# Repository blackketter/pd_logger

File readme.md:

# USB-C Power Delivery Measurement Tools

This repository contains two DIY gadgets to monitor and log **USB-C Power Delivery (PD)**.  
Both devices are designed to be easy to build, hackable, and useful for makers who want to explore USB-C PD.

---

## ✨ Features

- **DIY Power Meter**  
  Small device with an OLED display showing **voltage, current, and power** in real time.  
  Powered by an STM32 microcontroller.

- **PD Logger**  
  Wi-Fi enabled device based on ESP-01s.  
  Logs **voltage, current, and power** for several hours and serves interactive plots in any web browser.

---

## 📷 Devices

### Power Meter

### PD Logger

---

## 🛠️ How it works

- **USB-C connectors**: male on the input side, female on the output side.  
- **CC & VCONN lines** are passed through to handle PD voltage negotiation.  
- **Shunt resistor (50 mΩ)** allows precise current measurement.  
- **INA219 sensor** measures voltage and current via I²C.  
- **Step-down converter** generates 3.3 V from 5–20 V input.  
- **MCUs**: STM32 with OLED display (Power Meter), ESP-01s with Wi-Fi (PD Logger).  

---

## 📦 Hardware

- **Schematics & PCB files** → in this repo (`/electronics`)  
- **PCBs manufactured by** [JLCPCB](https://jlcpcb.com)  
- **3D printable cases** → in `/mechanics`  
- **Firmware** → in `/software`

All production data is included in `/electronics` so you can **order, print, and build your own devices**.

---

## 🌐 Usage

- **Power Meter**: plug between charger and device → read values on the display.  
- **PD Logger**: connect to your local Wi-Fi, then open `http://pd-logger.local` → see live values.  
  - Update interval: 5 seconds  
  - Logging capacity: several hours  
  - Data download as CSV file  
  - Interactive plots for Voltage / Current / Power over time  

---

## 📄 License

This project is licensed under the  
**Creative Commons Attribution-NonCommercial-ShareAlike 4.0 International (CC BY-NC-SA 4.0)** license.  

You are free to **share and adapt** the material, **for non-commercial purposes only**,  
as long as you provide proper attribution and distribute your contributions under the same license.  

For details, see the [LICENSE](LICENSE) file.  

---

## 🙌 Acknowledgments

- [Hackaday CH224K USB PD Decoy project](https://hackaday.io/) for inspiration

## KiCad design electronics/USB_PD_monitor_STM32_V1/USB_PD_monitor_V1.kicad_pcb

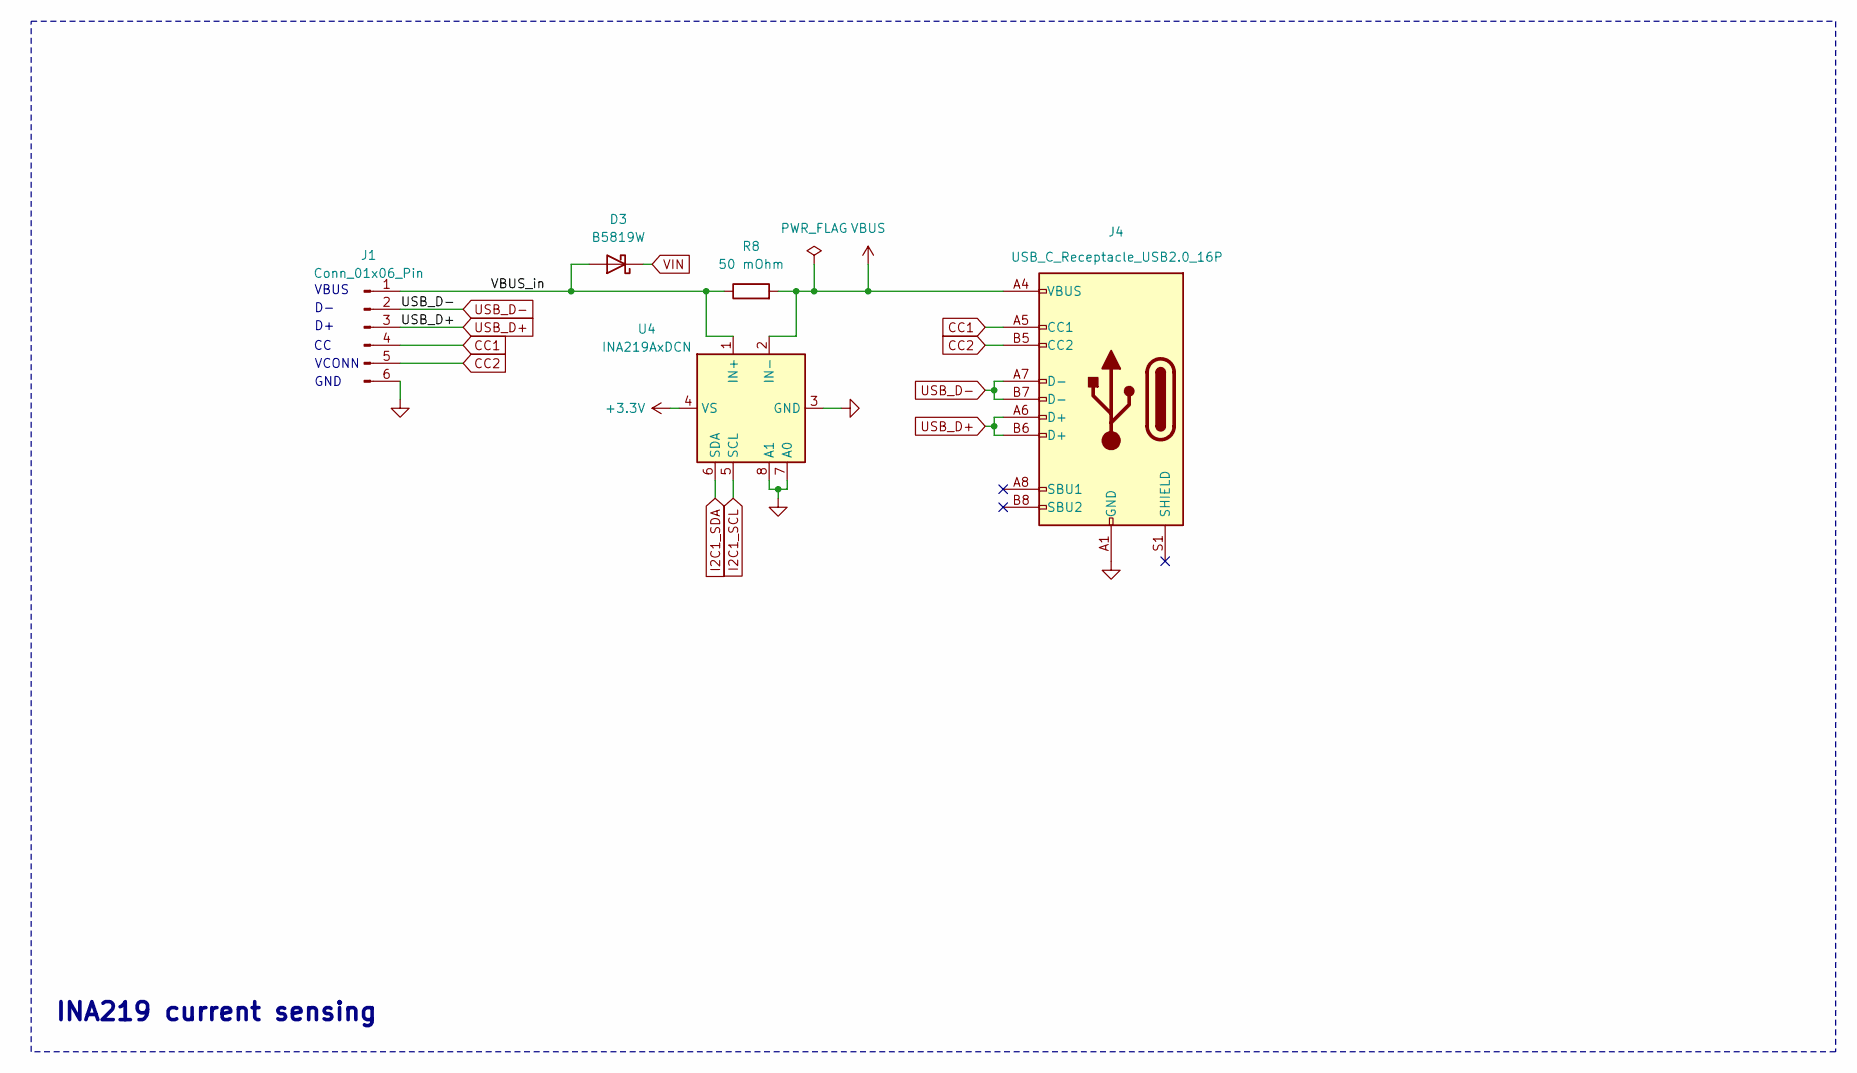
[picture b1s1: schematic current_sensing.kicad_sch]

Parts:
D3: B5819W; D_SOD-123; LCSC C8598
J1: Conn_01x06_Pin; header_90degree_01x06_back
J4: USB_C_Receptacle_USB2.0_16P; USB_C_Receptacle; LCSC C709357
R8: 50 mOhm; R_2512_6332Metric; LCSC C154681
U4: INA219AxDCN; SOT-23-8; LCSC C87469

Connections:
+3.3V: U4.4 (VS); also elsewhere on the board
/current_sensing/VBUS_in: D3.2 (A), J1.1, R8.1, U4.1 (IN+)
CC1: J1.4, J4.A5 (CC1)
CC2: J1.5, J4.B5 (CC2)
GND: J1.6, J4.A1 (GND), J4.A12 (GND), J4.B1 (GND), J4.B12 (GND), U4.3 (GND), U4.7 (A0), U4.8 (A1); also elsewhere on the board
I2C1_SCL: U4.5 (SCL); also elsewhere on the board
I2C1_SDA: U4.6 (SDA); also elsewhere on the board
USB_D+: J1.3, J4.A6 (D+), J4.B6 (D+)
USB_D-: J1.2, J4.A7 (D-), J4.B7 (D-)
VBUS: J4.A4 (VBUS), J4.A9 (VBUS), J4.B4 (VBUS), J4.B9 (VBUS), R8.2, U4.2 (IN-)
VIN: D3.1 (K); also elsewhere on the board

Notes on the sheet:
VBUS
VCONN
GND
INA219 current sensing

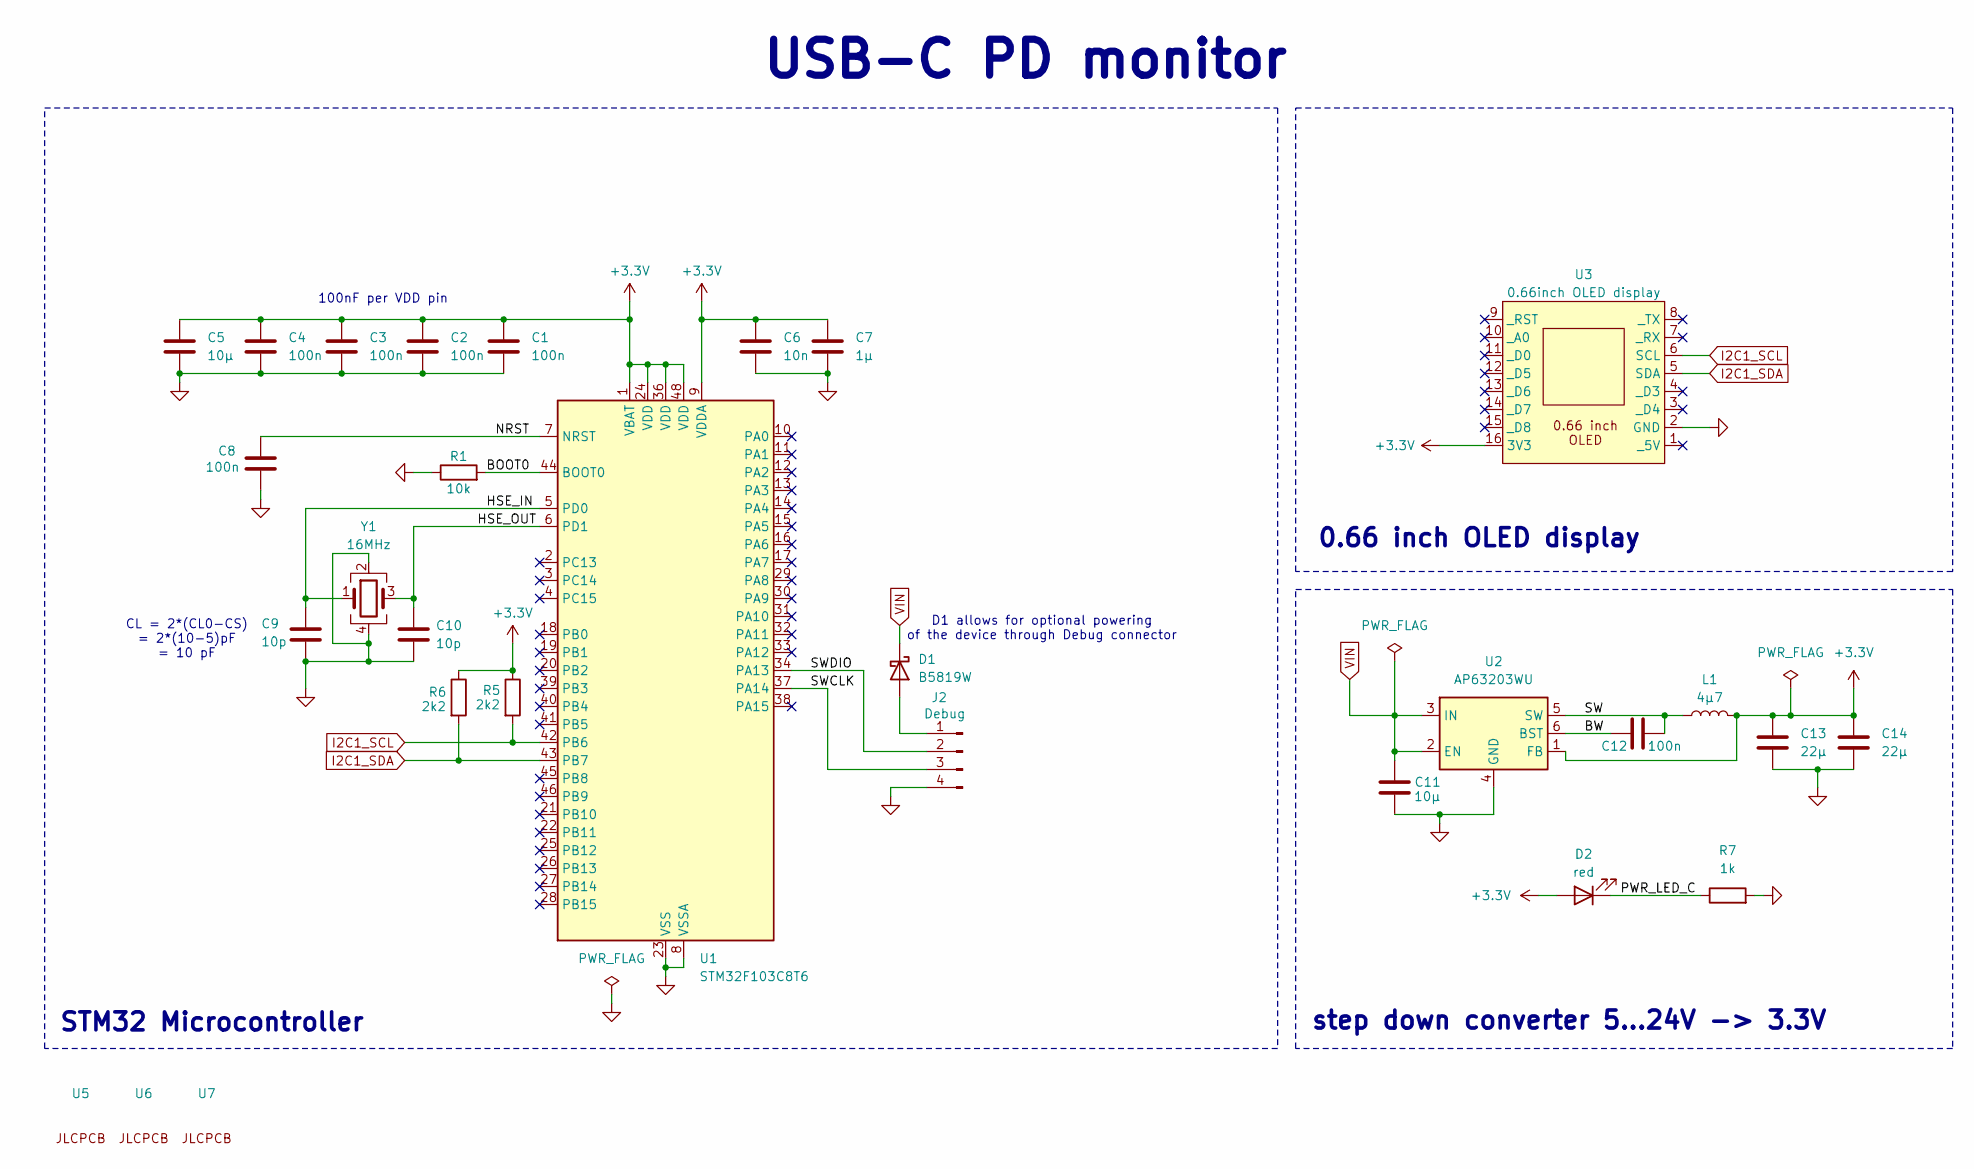
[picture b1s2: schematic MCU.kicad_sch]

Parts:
C1, C2, C3, C4, C8: 100n; C_0402_1005Metric; LCSC C1525
C5: 10µ; C_0603_1608Metric; LCSC C19702
C6: 10n; C_0402_1005Metric; LCSC C15195
C7: 1µ; C_0603_1608Metric; LCSC C15849
C9, C10: 10p; C_0402_1005Metric; LCSC C32949
C11: 10µ; C_0805_2012Metric; LCSC C440198
C12: 100n; C_0603_1608Metric; LCSC C14663
C13, C14: 22µ; C_0805_2012Metric; LCSC C45783
D1: B5819W; D_SOD-123; LCSC C8598
D2: red; LED_0603_1608Metric; LCSC C2286
J2: Debug; 4pin
L1: 4µ7; L_APV_APH0420; LCSC C133193
R1: 10k; R_0603_1608Metric; LCSC C25804
R5, R6: 2k2; R_0402_1005Metric; LCSC C25879
R7: 1k; R_0402_1005Metric; LCSC C11702
U1: STM32F103C8T6; LQFP-48_7x7mm_P0.5mm; LCSC C8734
U2: AP63203WU; TSOT-23-6; LCSC C780769
U3: 0.66inch OLED display; OLED_display_0_66
U5, U6, U7: JLC_tooling_hole
Y1: 16MHz; Crystal_SMD_3225-4Pin_3.2x2.5mm; LCSC C112972

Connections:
+3.3V: C1.1, C2.1, C3.1, C4.1, C5.1, C6.1, C7.1, C13.1, C14.1, D2.2 (A), L1.2, R5.1, R6.1, U1.1 (VBAT), U1.9 (VDDA), U1.24 (VDD), U1.36 (VDD), U1.48 (VDD), U2.1 (FB), U3.16 (3V3); also elsewhere on the board
/MCU/BOOT0: R1.2, U1.44 (BOOT0)
/MCU/BW: C12.1, U2.6 (BST)
/MCU/HSE_IN: C9.1, U1.5 (PD0), Y1.1
/MCU/HSE_OUT: C10.1, U1.6 (PD1), Y1.3
/MCU/NRST: C8.1, U1.7 (NRST)
/MCU/PWR_LED_C: D2.1 (K), R7.1
/MCU/SW: C12.2, L1.1, U2.5 (SW)
/MCU/SWCLK: J2.3, U1.37 (PA14)
/MCU/SWDIO: J2.2, U1.34 (PA13)
GND: C1.2, C2.2, C3.2, C4.2, C5.2, C6.2, C7.2, C8.2, C9.2, C10.2, C11.2, C13.2, C14.2, J2.4, R1.1, R7.2, U1.8 (VSSA), U1.23 (VSS), U1.35 (VSS), U1.47 (VSS), U2.4 (GND), U3.2 (GND), Y1.2, Y1.4; also elsewhere on the board
I2C1_SCL: R5.2, U1.42 (PB6), U3.6 (SCL); also elsewhere on the board
I2C1_SDA: R6.2, U1.43 (PB7), U3.5 (SDA); also elsewhere on the board
unnamed: D1.2 (A), J2.1
VIN: C11.1, D1.1 (K), U2.2 (EN), U2.3 (IN); also elsewhere on the board

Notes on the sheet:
100nF per VDD pin
step down converter 5...24V -> 3.3V
CL = 2*(CL0-CS) = 2*(10-5)pF = 10 pF
D1 allows for optional powering of the device through Debug connector
0.66 inch OLED display
STM32 Microcontroller
USB-C PD monitor

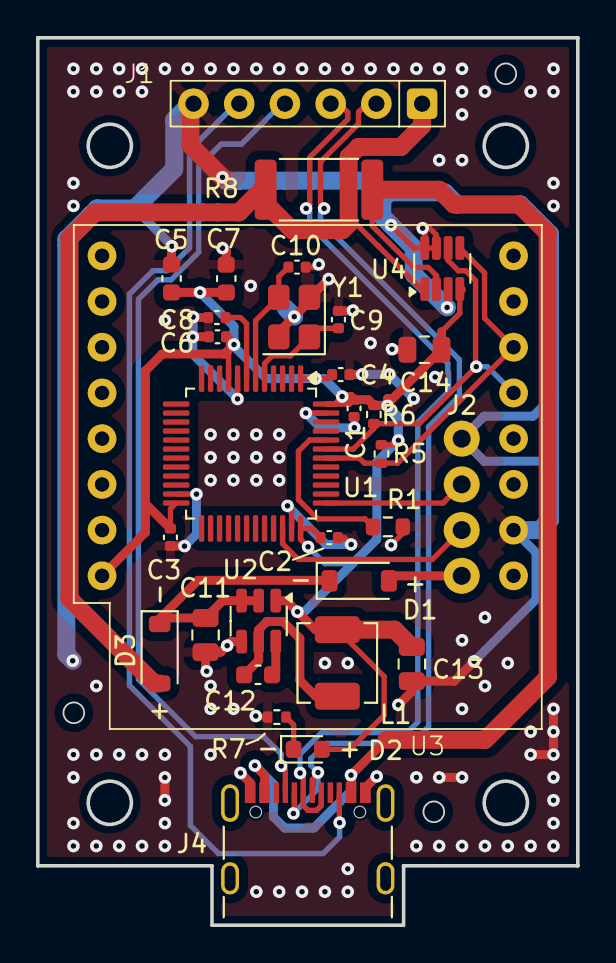
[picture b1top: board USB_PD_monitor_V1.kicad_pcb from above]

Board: 2 copper layers, 30.0 x 49.3 mm, 34 parts (0 on the bottom side), 21 nets.

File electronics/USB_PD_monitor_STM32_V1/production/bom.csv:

Designator,Footprint,Quantity,Value,LCSC Part #
"C1, C2, C3, C4, C8",0402,5,100n,C1525
"C10, C9",0402,2,10p,C32949 
C11,0805,1,10µ,C440198
C12,0603,1,100n,C14663
"C13, C14",0805,2,22µ,C45783
C5,0603,1,10µ,C19702 
C6,0402,1,10n,C15195
C7,0603,1,1µ,C15849
"D1, D3",D_SOD-123,2,B5819W,C8598
D2,0603,1,red,C2286
J1,header_90degree_01x06_back,1,Conn_01x06_Pin,
J2,4pin,1,Debug,
J4,USB_C_Receptacle,1,USB_C_Receptacle_USB2.0_16P,C709357
L1,L_APV_APH0420,1,4µ7,C133193
R1,0603,1,10k,C25804 
"R5, R6",0402,2,2k2,C25879
R7,0402,1,1k,C11702
R8,2512,1,50 mOhm,C154681
U1,LQFP-48_7x7mm_P0.5mm,1,STM32F103C8T6,C8734
U2,TSOT-23-6,1,AP63203WU,C780769
U3,OLED_display_0_66,1,0.66inch OLED display,
U4,SOT-23-8,1,INA219AxDCN,C87469
"U5, U6, U7",JLC_tooling_hole,3,~,
Y1,Crystal_SMD_3225-4Pin_3.2x2.5mm,1,16MHz,C112972

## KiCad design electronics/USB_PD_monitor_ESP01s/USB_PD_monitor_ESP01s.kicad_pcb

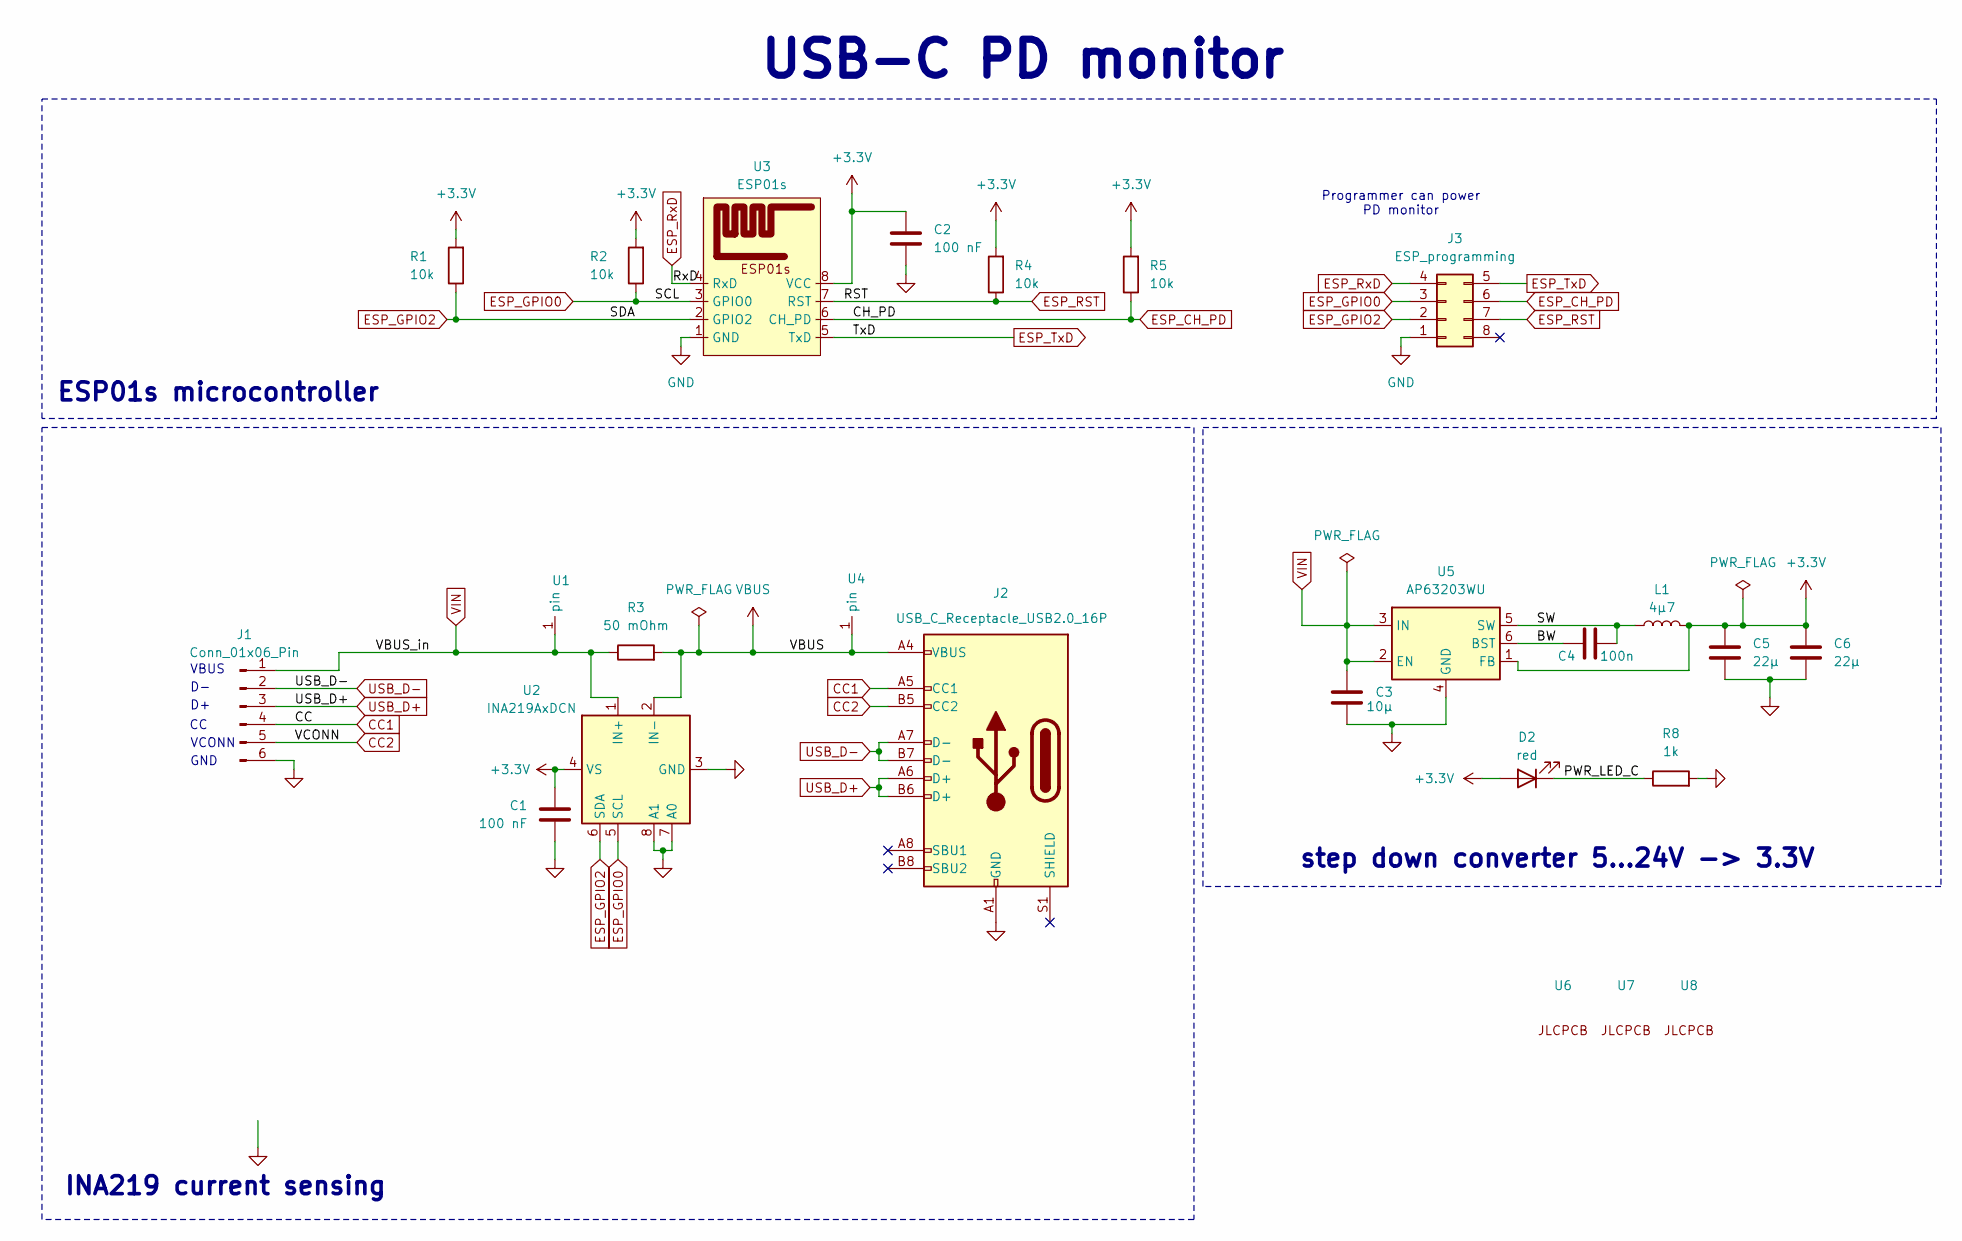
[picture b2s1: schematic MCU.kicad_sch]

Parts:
C1, C2: 100 nF; C_0402_1005Metric; LCSC C1525
C3: 10µ; C_0805_2012Metric; LCSC C440198
C4: 100n; C_0603_1608Metric; LCSC C14663
C5, C6: 22µ; C_0805_2012Metric; LCSC C45783
D2: red; LED_0603_1608Metric; LCSC C2286
J1: Conn_01x06_Pin; header_90degree_01x06_back
J2: USB_C_Receptacle_USB2.0_16P; USB_C_Receptacle; LCSC C709357
J3: ESP_programming; Header_ESP01
L1: 4µ7; L_APV_APH0420; LCSC C133193
R1, R2, R4, R5: 10k; R_0402_1005Metric; LCSC C25744
R3: 50 mOhm; R_2512_6332Metric; LCSC C154681
R8: 1k; R_0402_1005Metric; LCSC C11702
U1, U4: 1pin
U2: INA219AxDCN; SOT-23-8; LCSC C87469
U3: ESP01s; ESP-01
U5: AP63203WU; TSOT-23-6; LCSC C780769
U6, U7, U8: JLC_tooling_hole

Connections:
+3.3V: C1.1, C2.1, C5.1, C6.1, D2.2 (A), L1.2, R1.2, R2.2, R4.2, R5.2, U2.4 (VS), U3.8 (VCC), U5.1 (FB)
/MCU/BW: C4.1, U5.6 (BST)
/MCU/PWR_LED_C: D2.1 (K), R8.1
/MCU/SW: C4.2, L1.1, U5.5 (SW)
CC1: J1.4, J2.A5 (CC1)
CC2: J1.5, J2.B5 (CC2)
ESP_CH_PD: J3.6, R5.1, U3.6 (CH_PD)
ESP_GPIO0: J3.3, R2.1, U2.5 (SCL), U3.3 (GPIO0)
ESP_GPIO2: J3.2, R1.1, U2.6 (SDA), U3.2 (GPIO2)
ESP_RST: J3.7, R4.1, U3.7 (RST)
ESP_RxD: J3.4, U3.4 (RxD)
ESP_TxD: J3.5, U3.5 (TxD)
GND: C1.2, C2.2, C3.2, C5.2, C6.2, J1.6, J2.A1 (GND), J2.A12 (GND), J2.B1 (GND), J2.B12 (GND), J3.1, R8.2, U2.3 (GND), U2.7 (A0), U2.8 (A1), U3.1 (GND), U5.4 (GND)
USB_D+: J1.3, J2.A6 (D+), J2.B6 (D+)
USB_D-: J1.2, J2.A7 (D-), J2.B7 (D-)
VBUS: J2.A4 (VBUS), J2.A9 (VBUS), J2.B4 (VBUS), J2.B9 (VBUS), R3.2, U2.2 (IN-), U4.1 (pin)
VIN: C3.1, J1.1, R3.1, U1.1 (pin), U2.1 (IN+), U5.2 (EN), U5.3 (IN)

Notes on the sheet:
VCONN
VBUS
Programmer can power PD monitor
step down converter 5...24V -> 3.3V
GND
INA219 current sensing
ESP01s microcontroller
USB-C PD monitor

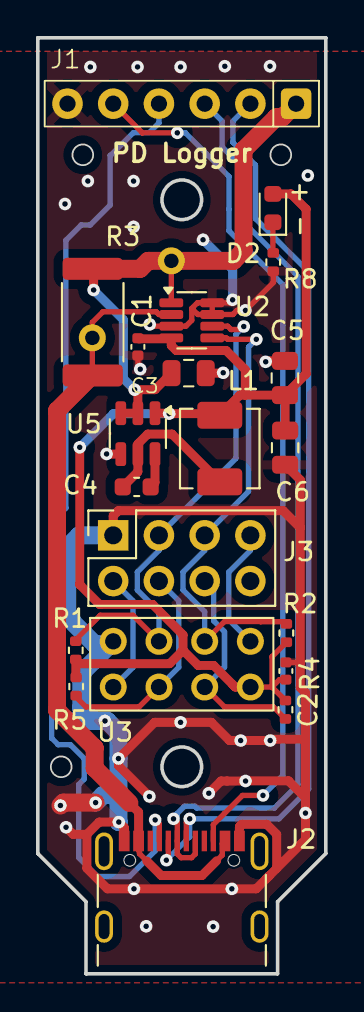
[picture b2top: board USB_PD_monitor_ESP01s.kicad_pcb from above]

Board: 2 copper layers, 16.0 x 52.0 mm, 25 parts (0 on the bottom side), 17 nets.

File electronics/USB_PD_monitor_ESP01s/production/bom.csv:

Designator,Footprint,Quantity,Value,LCSC Part #
"C1, C2",0402,2,100 nF,C1525
C3,0805,1,10µ,C440198
C4,0603,1,100n,C14663
"C5, C6",0805,2,22µ,C45783
D2,0603,1,red,C2286
J1,header_90degree_01x06_back,1,Conn_01x06_Pin,
J2,USB_C_Receptacle,1,USB_C_Receptacle_USB2.0_16P,C709357
J3,Header_ESP01,1,ESP_programming,
L1,L_APV_APH0420,1,4µ7,C133193
"R1, R2, R4, R5",0402,4,10k,C25744
R3,2512,1,50 mOhm,C154681
R8,0402,1,1k,C11702
"U1, U4",1pin,2,~,
U2,SOT-23-8,1,INA219AxDCN,C87469
U3,ESP-01,1,ESP01s,
U5,TSOT-23-6,1,AP63203WU,C780769
"U6, U7, U8",JLC_tooling_hole,3,~,

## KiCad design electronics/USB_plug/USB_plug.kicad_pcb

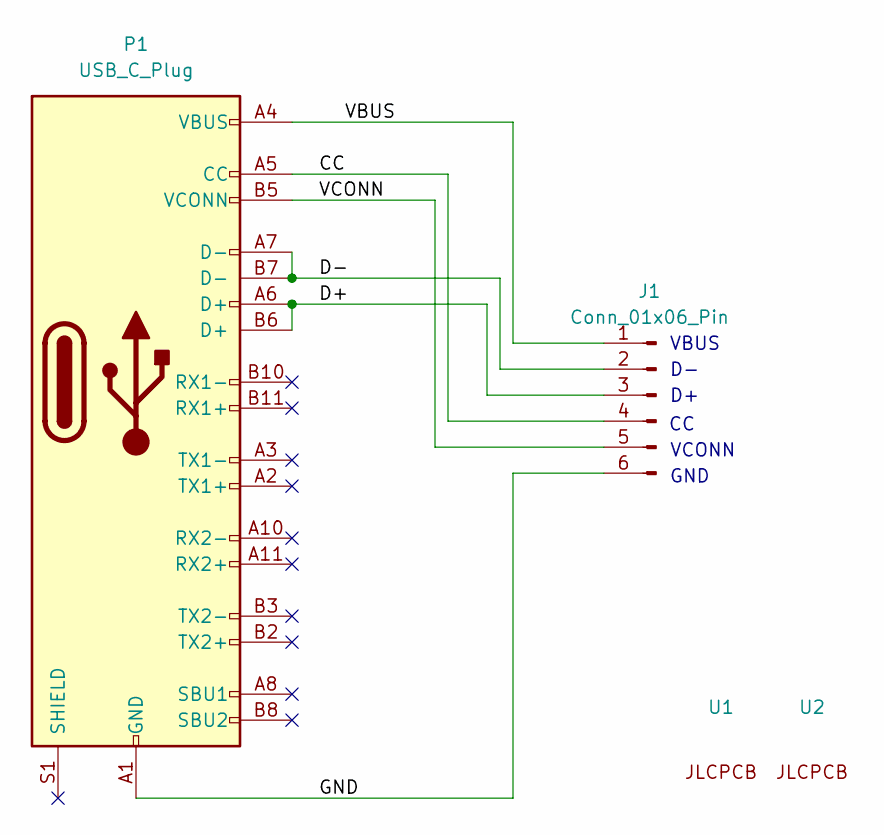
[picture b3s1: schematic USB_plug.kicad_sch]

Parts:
J1: Conn_01x06_Pin; header_01x06
P1: USB_C_Plug; C168690; LCSC C168690
U1, U2: JLC_tooling_hole

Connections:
/CC: J1.4, P1.A5 (CC)
/D+: J1.3, P1.A6 (D+), P1.B6 (D+)
/D-: J1.2, P1.A7 (D-), P1.B7 (D-)
/GND: J1.6, P1.A1 (GND), P1.A12 (GND), P1.B1 (GND), P1.B12 (GND)
/VBUS: J1.1, P1.A4 (VBUS), P1.A9 (VBUS), P1.B4 (VBUS), P1.B9 (VBUS)
/VCONN: J1.5, P1.B5 (VCONN)

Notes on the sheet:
VCONN
GND
VBUS

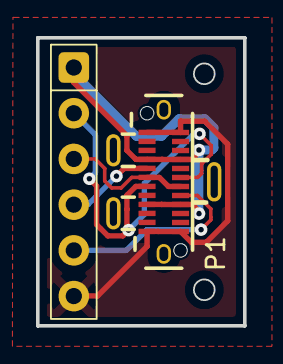
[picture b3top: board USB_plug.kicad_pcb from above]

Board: 2 copper layers, 11.5 x 16.0 mm, 4 parts (0 on the bottom side), 6 nets.

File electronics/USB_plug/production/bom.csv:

Designator,Footprint,Quantity,Value,LCSC Part #
J1,header_01x06,1,Conn_01x06_Pin,
P1,C168690,1,USB_C_Plug,C168690
"U1, U2",JLC_tooling_hole,2,~,

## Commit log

2025-09-10 various improvements. Both pd_logger and power_meter fully functional
2025-09-10 3d print files added
2025-09-10 add readme.md
2025-09-10 update images
2025-09-15 Ignore .DS_Store files
2025-09-16 Add .gitignore to exclude .DS_Store
